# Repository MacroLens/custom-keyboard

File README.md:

# custom-keyboard
A custom mechanical keyboard I am making from scratch. The PCB will have functionality for Bluetooth LE, an LED matrix and USB-C outputs. Based on the AVR micro-controller family.

</img>

Thanks to [PCBWAY](https://www.pcbway.com/) for sending me some prototypes!

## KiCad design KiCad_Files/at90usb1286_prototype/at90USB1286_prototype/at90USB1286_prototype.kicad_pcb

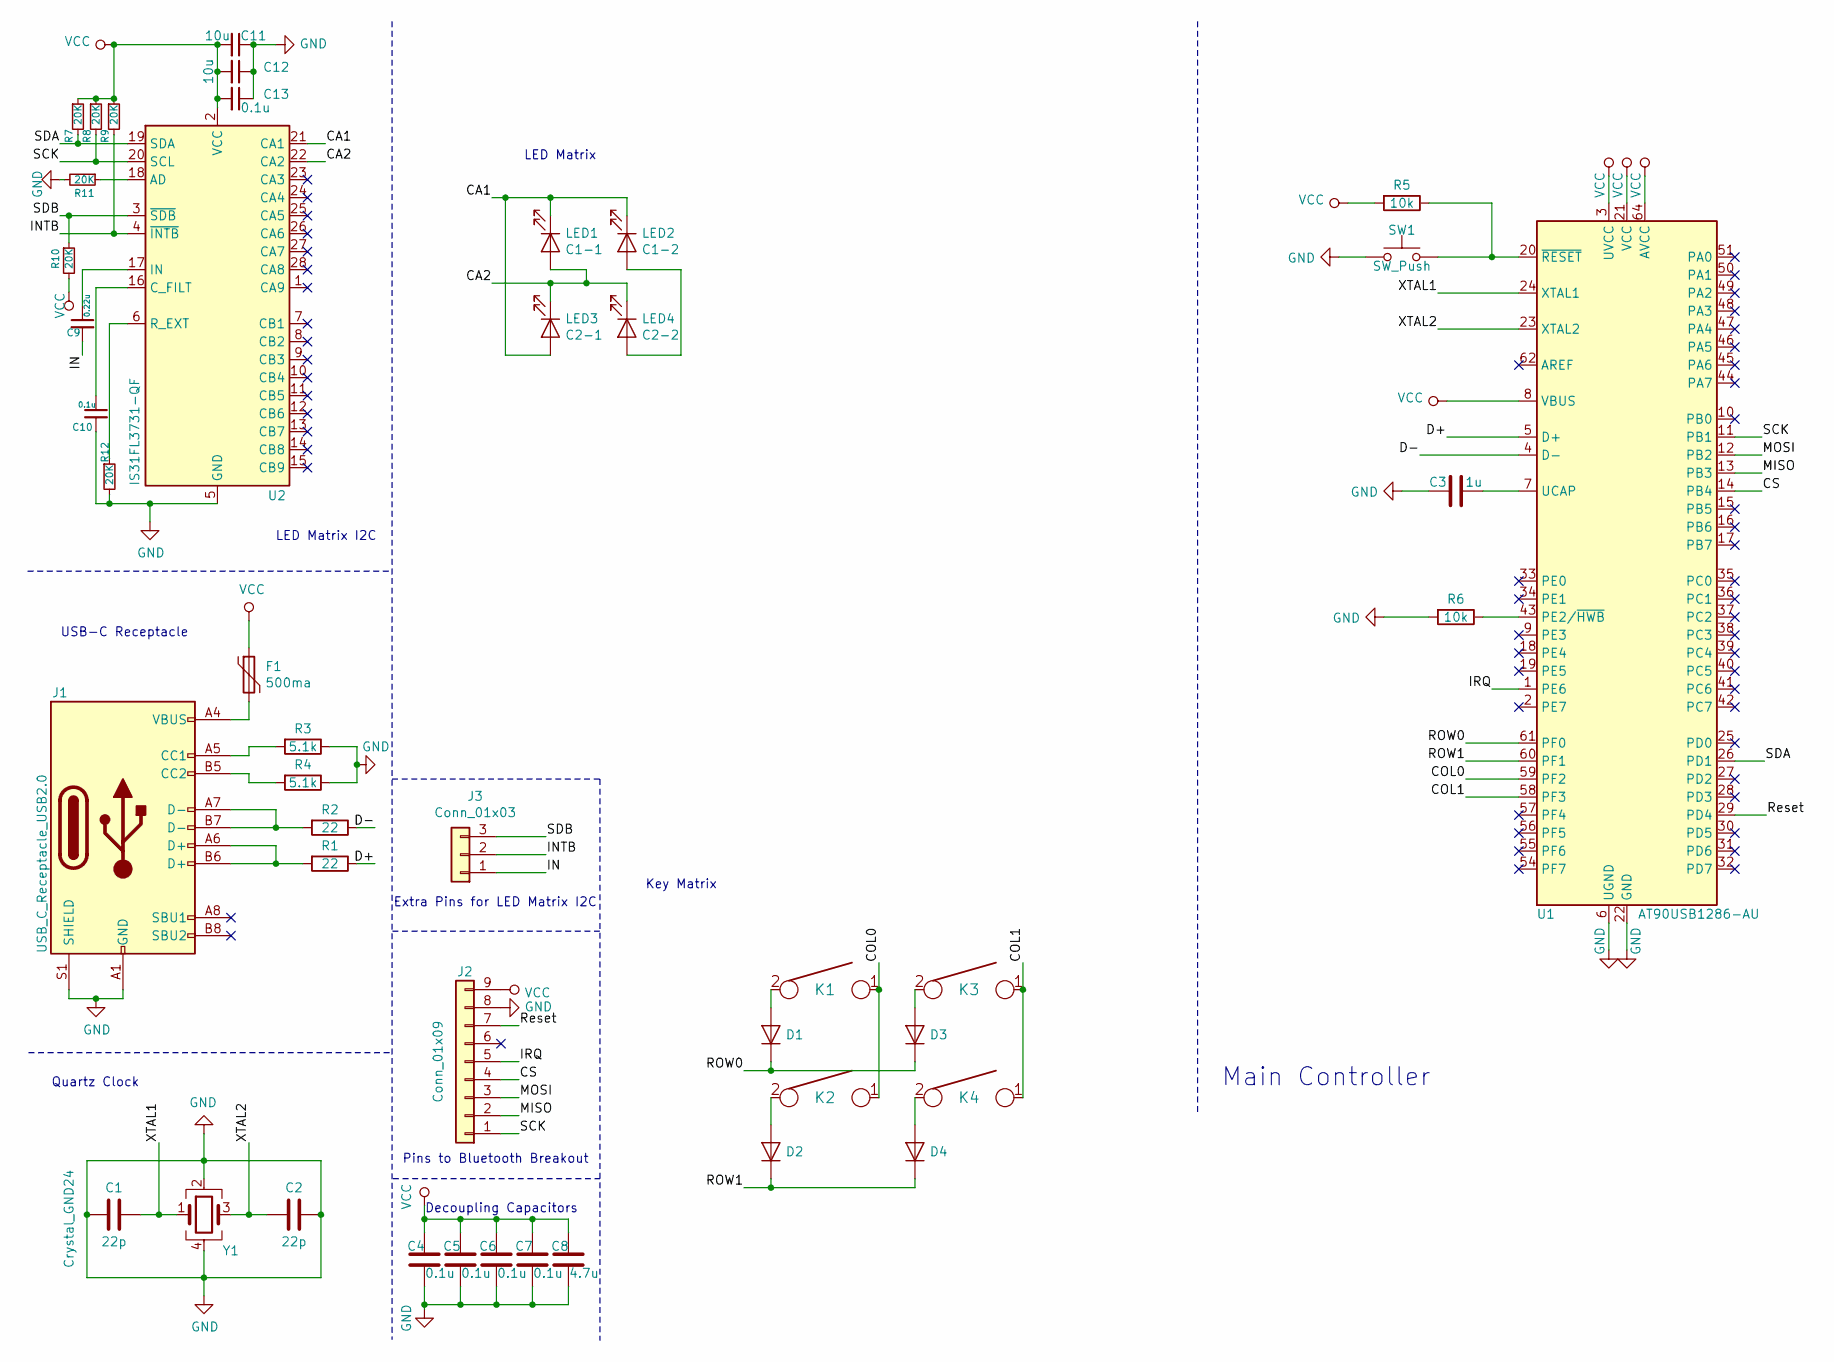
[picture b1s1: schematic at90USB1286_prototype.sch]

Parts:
C1, C2: 22p; C_0805_2012Metric_Pad1.15x1.40mm_HandSolder
C3: 1u; C_0805_2012Metric_Pad1.15x1.40mm_HandSolder
C4, C5, C6, C7, C10, C13: 0.1u; C_0805_2012Metric_Pad1.15x1.40mm_HandSolder
C8: 4.7u; C_0805_2012Metric_Pad1.15x1.40mm_HandSolder
C9: 0.22u; C_0805_2012Metric_Pad1.15x1.40mm_HandSolder
C11, C12: 10u; C_0805_2012Metric_Pad1.15x1.40mm_HandSolder
D1, D2, D3, D4: D; D_0805_2012Metric_Pad1.15x1.40mm_HandSolder
F1: 500ma; Fuse_0805_2012Metric_Pad1.15x1.40mm_HandSolder
J1: USB_C_Receptacle_USB2.0; USB_C_Receptacle_Amphenol_12401610E4-2A
J2: Conn_01x09; PinHeader_1x09_P1.27mm_Vertical
J3: Conn_01x03; PinHeader_1x03_P1.27mm_Vertical
K1, K2, K3, K4: KEYSW; SW_Cherry_MX_1.00u_Plate
LED1: C1-1; LED_D1.8mm_W3.3mm_H2.4mm
LED2: C1-2; LED_D1.8mm_W3.3mm_H2.4mm
LED3: C2-1; LED_D1.8mm_W3.3mm_H2.4mm
LED4: C2-2; LED_D1.8mm_W3.3mm_H2.4mm
R1, R2: 22; R_0805_2012Metric_Pad1.15x1.40mm_HandSolder
R3, R4: 5.1k; R_0805_2012Metric_Pad1.15x1.40mm_HandSolder
R5, R6: 10k; R_0805_2012Metric_Pad1.15x1.40mm_HandSolder
R7, R8, R9, R10, R11, R12: 20K; R_0805_2012Metric_Pad1.15x1.40mm_HandSolder
SW1: SW_Push; SW_SPST_TL3342
U1: AT90USB1286-AU; TQFP-64_14x14mm_P0.8mm
U2: IS31FL3731-QF; QFN-28-1EP_4x4mm_P0.4mm_EP2.3x2.3mm
Y1: Crystal_GND24; Crystal_SMD_SeikoEpson_FA238V-4Pin_3.2x2.5mm

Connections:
/CA1: LED1.1 (K), LED2.1 (K), LED3.2 (A), U2.21 (CA1)
/CA2: LED1.2 (A), LED3.1 (K), LED4.1 (K), U2.22 (CA2)
/COL0: K1.1, K2.1, U1.59 (PF2)
/COL1: K3.1, K4.1, U1.58 (PF3)
/CS: J2.4, U1.14 (PB4)
/D+: R1.1, U1.5 (D+)
/D-: R2.1, U1.4 (D-)
/IN: C9.2, J3.1
/INTB: J3.2, R9.2, U2.4 (~INTB)
/IRQ: J2.5, U1.1 (PE6)
/MISO: J2.2, U1.13 (PB3)
/MOSI: J2.3, U1.12 (PB2)
/ROW0: D1.1 (K), D3.1 (K), U1.61 (PF0)
/ROW1: D2.1 (K), D4.1 (K), U1.60 (PF1)
/Reset: J2.7, U1.29 (PD4)
/SCK: J2.1, R8.2, U1.11 (PB1), U2.20 (SCL)
/SDA: R7.2, U1.26 (PD1), U2.19 (SDA)
/SDB: J3.3, R10.1, U2.3 (~SDB)
/XTAL1: C1.1, U1.24 (XTAL1), Y1.1
/XTAL2: C2.2, U1.23 (XTAL2), Y1.3
GND: C1.2, C2.1, C3.2, C4.2, C5.2, C6.2, C7.2, C8.2, C10.2, C11.1, C12.1, C13.1, J1.A1 (GND), J1.A12 (GND), J1.B1 (GND), J1.B12 (GND), J1.S1 (SHIELD), J2.8, R3.1, R4.1, R6.2, R11.2, R12.2, SW1.1, U1.6 (UGND), U1.22 (GND), U1.53 (GND), U1.63 (GND), U2.5 (GND), U2.29 (GND), Y1.2, Y1.4
unnamed: C3.1, U1.7 (UCAP)
unnamed: C9.1, U2.17 (IN)
unnamed: C10.1, U2.16 (C_FILT)
unnamed: D1.2 (A), K1.2
unnamed: D2.2 (A), K2.2
unnamed: D3.2 (A), K3.2
unnamed: D4.2 (A), K4.2
unnamed: F1.2, J1.A4 (VBUS), J1.A9 (VBUS), J1.B4 (VBUS), J1.B9 (VBUS)
unnamed: J1.A5 (CC1), R3.2
unnamed: J1.A6 (D+), J1.B6 (D+), R1.2
unnamed: J1.A7 (D-), J1.B7 (D-), R2.2
unnamed: J1.B5 (CC2), R4.2
unnamed: LED2.2 (A), LED4.2 (A)
unnamed: R5.1, SW1.2, U1.20 (~RESET)
unnamed: R6.1, U1.43 (PE2/~HWB)
unnamed: R11.1, U2.18 (AD)
unnamed: R12.1, U2.6 (R_EXT)
VCC: C4.1, C5.1, C6.1, C7.1, C8.1, C11.2, C12.2, C13.2, F1.1, J2.9, R5.2, R7.1, R8.1, R9.1, R10.2, U1.3 (UVCC), U1.8 (VBUS), U1.21 (VCC), U1.52 (VCC), U1.64 (AVCC), U2.2 (VCC)

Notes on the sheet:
Quartz Clock
Decoupling Capacitors
USB-C Receptacle
Pins to Bluetooth Breakout
Main Controller
LED Matrix I2C
LED Matrix
Extra Pins for LED Matrix I2C
Key Matrix

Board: 2 copper layers, 45 parts (0 on the bottom side), 39 nets, no tracks yet.

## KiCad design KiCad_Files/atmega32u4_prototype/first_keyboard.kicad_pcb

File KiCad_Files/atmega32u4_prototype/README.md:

This is a KiCad project folder with my original prototype. It uses some libraries it might not need and was based heavily on [ruiqimao's guide](https://github.com/ruiqimao/keyboard-pcb-guide/blob/master/README.md) with some minor tweaks.

*Note*
The diodes are on the wrong side and the footprint has no capability for LEDs.Which the future prototype will address.

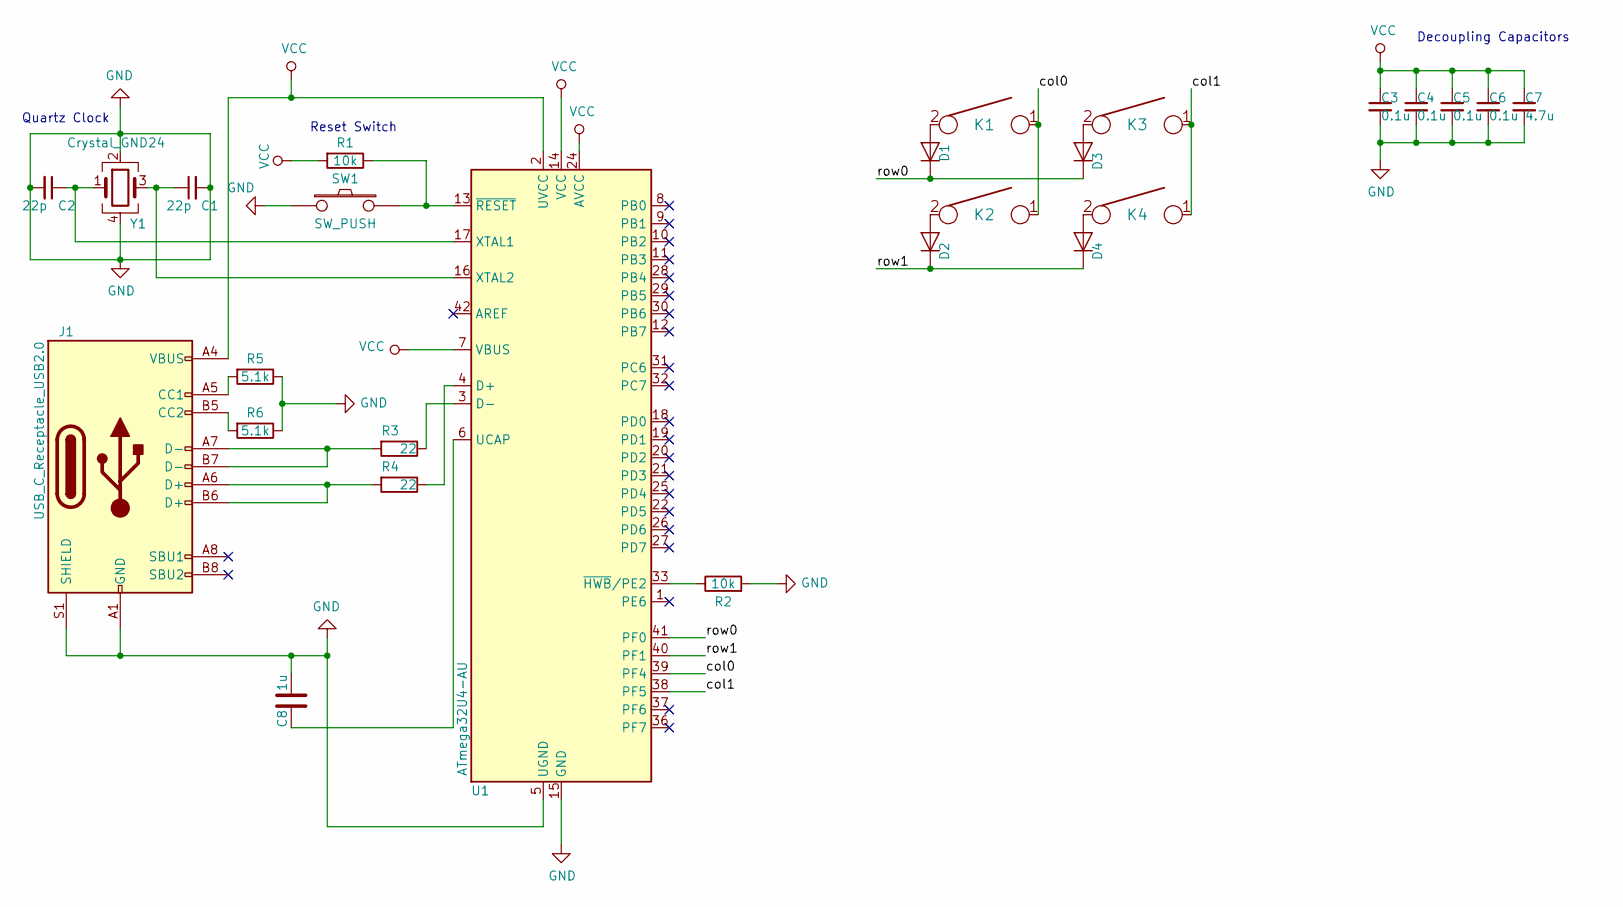
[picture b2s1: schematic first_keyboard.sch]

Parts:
C1, C2: 22p; C_0805_2012Metric_Pad1.15x1.40mm_HandSolder
C3, C4, C5, C6: 0.1u; C_0805_2012Metric_Pad1.15x1.40mm_HandSolder
C7: 4.7u; C_0805_2012Metric_Pad1.15x1.40mm_HandSolder
C8: 1u; C_0805_2012Metric_Pad1.15x1.40mm_HandSolder
D1, D2, D3, D4: D; D_SOD123_axial
J1: USB_C_Receptacle_USB2.0; USB_C_Receptacle_Amphenol_12401610E4-2A
K1, K2, K3, K4: KEYSW; Mx_Alps_100
R1, R2: 10k; R_0805_2012Metric_Pad1.15x1.40mm_HandSolder
R3, R4: 22; R_0805_2012Metric_Pad1.15x1.40mm_HandSolder
R5, R6: 5.1k; R_0805_2012Metric_Pad1.15x1.40mm_HandSolder
SW1: SW_PUSH; SW_SPST_TL3342
U1: ATmega32U4-AU; TQFP-44_10x10mm_P0.8mm
Y1: Crystal_GND24; Crystal_SMD_SeikoEpson_FA238-4Pin_3.2x2.5mm

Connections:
/col0: K1.1, K2.1, U1.39 (PF4)
/col1: K3.1, K4.1, U1.38 (PF5)
/row0: D1.1 (K), D3.1 (K), U1.41 (PF0)
/row1: D2.1 (K), D4.1 (K), U1.40 (PF1)
GND: C1.2, C2.2, C3.2, C4.2, C5.2, C6.2, C7.2, C8.2, J1.A1 (GND), J1.A12 (GND), J1.B1 (GND), J1.B12 (GND), J1.S1 (SHIELD), R2.2, R5.1, R6.1, SW1.1, U1.5 (UGND), U1.15 (GND), U1.23 (GND), U1.35 (GND), U1.43 (GND), Y1.2, Y1.4
unnamed: C1.1, U1.16 (XTAL2), Y1.3
unnamed: C2.1, U1.17 (XTAL1), Y1.1
unnamed: C8.1, U1.6 (UCAP)
unnamed: D1.2 (A), K1.2
unnamed: D2.2 (A), K2.2
unnamed: D3.2 (A), K3.2
unnamed: D4.2 (A), K4.2
unnamed: J1.A5 (CC1), R5.2
unnamed: J1.A6 (D+), J1.B6 (D+), R4.2
unnamed: J1.A7 (D-), J1.B7 (D-), R3.2
unnamed: J1.B5 (CC2), R6.2
unnamed: R1.1, SW1.2, U1.13 (~RESET)
unnamed: R2.1, U1.33 (~HWB~/PE2)
unnamed: R3.1, U1.3 (D-)
unnamed: R4.1, U1.4 (D+)
VCC: C3.1, C4.1, C5.1, C6.1, C7.1, J1.A4 (VBUS), J1.A9 (VBUS), J1.B4 (VBUS), J1.B9 (VBUS), R1.2, U1.2 (UVCC), U1.7 (VBUS), U1.14 (VCC), U1.24 (AVCC), U1.34 (VCC), U1.44 (AVCC)

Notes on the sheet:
Decoupling Capacitors
Reset Switch
Quartz Clock

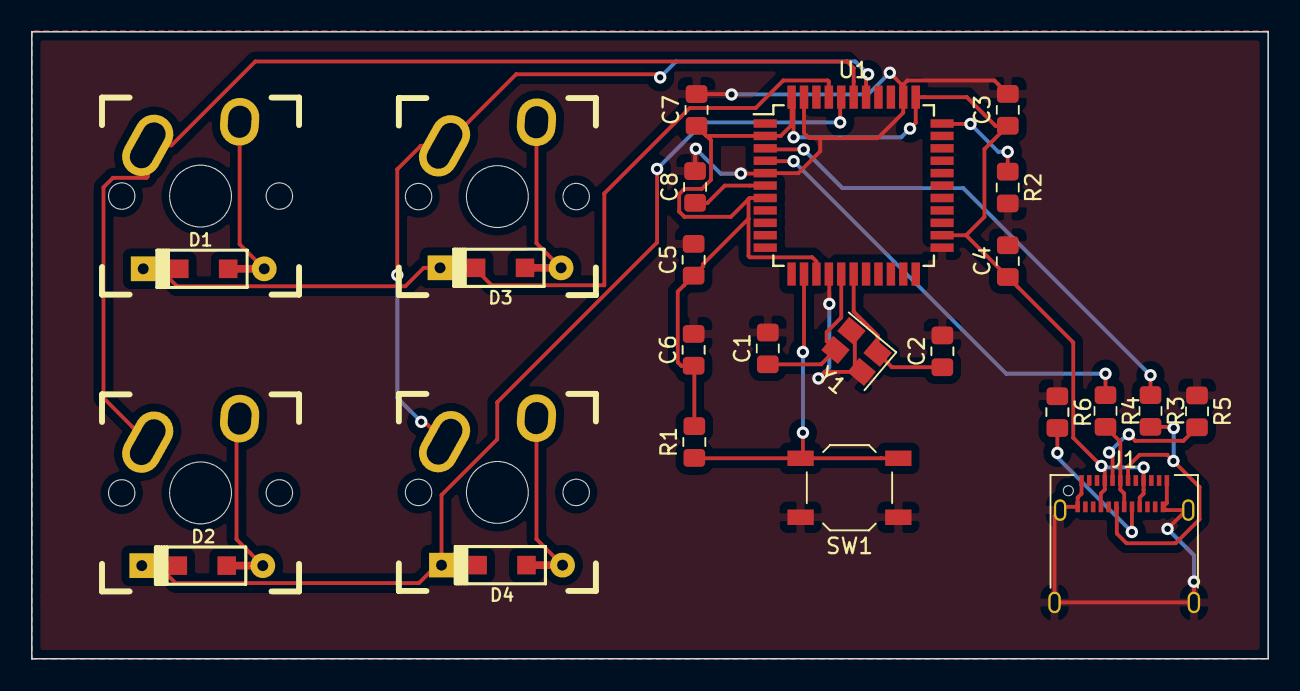
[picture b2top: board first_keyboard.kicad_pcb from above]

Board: 2 copper layers, 79.7 x 40.4 mm, 26 parts (0 on the bottom side), 21 nets.

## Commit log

2019-09-01 The first board I made to test whether I could properly wire the chip and if the USB-C Port works.
2019-09-01 Cleaning up unnecessary file
2019-09-01 Added a README for clarity of files.
2019-09-01 Getting rid of unnnecessary files.
2019-09-01 Getting rid of old Gerber files which could be generated by anyone.
2019-09-01 Old gerbers
2019-09-01 Replaced unarchived project with archived KiCad project.
2019-09-01 A parts list of all the components on the board. This can be uploaded to digikey for quick purchasing. There are extra components in the list just in case.
2019-09-01 Added QMK files to be used with the AtMega32u4 prototype.
2019-09-01 Added image
2019-09-01 Formatting
2019-09-01 fixed link
2019-09-02 New schematic with Bluetooth, LED matrix, and new chip.
2019-09-02 Working file removed
2019-09-03 Changed matrix I2C, and finished PCB
